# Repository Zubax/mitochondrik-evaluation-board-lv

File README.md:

# Mitochondrik Evaluation Board LV

Mitochondrik Evaluation Board LV is a basic reference design and an evaluation board for the
[Zubax Mitochnodrik LV](https://zubax.com/mitochondrik-lv) motor control module.
When combined with Mitochondrik LV, it makes a complete PMSM motor controller suitable for bench testing and evaluation of the
[Telega motor control technology](https://telega.zubax.com).
The device is also a specialized jig (fixture) that allows easy flashing and testing of all functions of Mitochondrik LV during manufacturing.

## Specifications

* Supply voltage range: 13--51 V.
* Max continuous current/peak phase current amplitude: 10/20 A.
* Designed strictly for indoor use.

### Telega configuration

In order to use the Mitochondrik Evaluation Board LV, the installed Mitochondrik LV has to be informed
of the parameters of the board.
To achieve this, upload the following configuration:

```yaml
# Mitochondrik Evaluation Board LV has transistors with R_DSon = 4 mohms, and 3 mohm shunts on phases A and B.
# Refer to the Mitochondrik-LV datasheet for the explanation of how the parameter values have been found.
vsi.bridge_resistance:    [0.004, 0.007, 0.004, 0.007, 0.004, 0.004]                            # [ohm]
vsi.phase_current_gain:   [33.333333333333, 33.333333333333, 8.333333333333, 8.333333333333]    # [ampere/volt]
vsi.phase_current_stderr: [0.2, 0.2, 0.1, 0.1]                                                  # [ampere]
vsi.thermistor_v2k:       [223.15, 100.0, 0.0]                                                  # for MCP9700

sys.debug: false            # Turn off the in-circuit debug interfaces to enhance EMI immunity.
sys.golden: sys. vsi.       # Retain these parameter groups across a factory reset.
```

Refer to the Telega Reference Manual for details.

## Features

All external signals of Mitochondrik LV are accessible via the pin headers.
Mitochondrik Evaluation Board LV also provides dedicated connectors for 2 Cyphal/CAN interfaces,
a Dronecode debug port, and one Aux connector for GPIO and RCPWM.
The motor phase wires and the DC link input are connected via M3 screw terminals.

A switch has been implemented which prevents powering the device if Mitochondrik LV is not installed or installed incorrectly.
Thanks to this feature, it is not required to remove the power supply every time before insertion of Mitochondrik LV.
The Mitochondrik presence pin is low when Mitochondrik is inserted.
Then, CAN_VDD should be set high, which turns on Q9, which then turns on Q11, allowing VDC to power the device.
The CAN_VDD is connected to the GPIO PA4 of Zubax Babel, which would turn on the power supply during testing.
The power supply switch is arranged in logic OR configuration, which means it's enable pin is attached to both of Babels
and either one of them can turn it on.
Check out the hardware schematic below:

A mechanical key is introduced to prevent incorrect insertion of Mitochondrik LV.

Headers are available to install the [Babel-Babel production tool](https://github.com/Zubax/Babel-Babel)
directly to the Mitochondrik Evaluation Board LV PCB without the need for an external adapter PCB.

| Stacked Babel-Babel | Babel-Babel headers |
| ------------------- | ------------------- |
|   |   |

## Manufacturing instructions

For details on the manufacturing process of the device, check the
instructions at [manufacturing document](/docs/manufacturing.md).

## Release notes

Newest entries at the top.

### Mitochondrik Evaluation Board LV v1.2 (2023)

* P-Channel mosfet for safety insertion changed from SQJ459EP-T1_GE3 to RQ3L070ATTB due to availability issue
* Alternative part added for FDMS86368-F085

### Mitochondrik Evaluation Board LV v1.1 (2023)

* Bug fix for CANVDD not connected to protection circuit
* Added CANVDD supply for consumer version
* Added connecto to adapter for ribbon to connect top part of adapter to the bottom part

### Mitochondrik Evaluation Board LV v1.0 (2021)

* The original version.

### License

This project is licensed under the terms of [CC-BY 4.0](https://creativecommons.org/licenses/by/4.0/).

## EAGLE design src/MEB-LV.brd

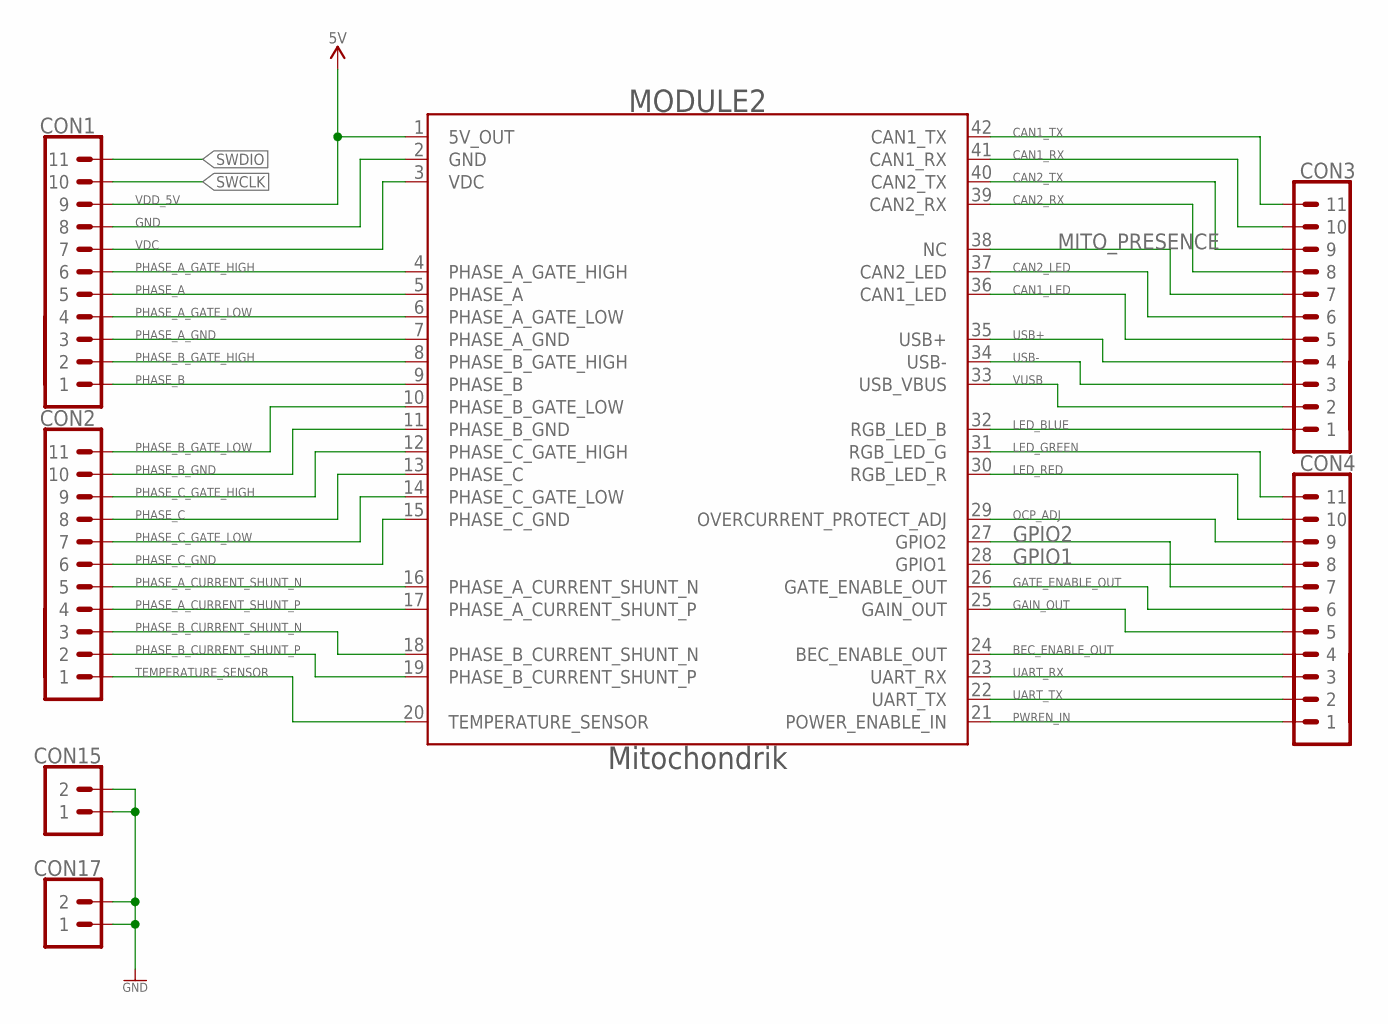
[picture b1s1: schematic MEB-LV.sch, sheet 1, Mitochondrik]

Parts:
CON1, CON2, CON3, CON4: PINHEAD_1X11-2.54_STRAIGHT_MALE; 1X11-PTH-2.54; DIGIKEY# S1022EC-11-ND
CON15, CON17: PINHEAD_1X02-2.54; 1X02-PTH-2.54; DIGIKEY# S1041E-02-ND
MODULE2: MITOCHONDRIK

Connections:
BEC_ENABLE_OUT: CON4.4, MODULE2.24 (BEC_ENABLE_OUT); also elsewhere on the board
CAN1_LED: CON3.5, MODULE2.36 (CAN1_LED); also elsewhere on the board
CAN1_RX: CON3.10, MODULE2.41 (CAN1_RX); also elsewhere on the board
CAN1_TX: CON3.11, MODULE2.42 (CAN1_TX); also elsewhere on the board
CAN2_LED: CON3.6, MODULE2.37 (CAN2_LED); also elsewhere on the board
CAN2_RX: CON3.8, MODULE2.39 (CAN2_RX); also elsewhere on the board
CAN2_TX: CON3.9, MODULE2.40 (CAN2_TX); also elsewhere on the board
GAIN_OUT: CON4.5, MODULE2.25 (GAIN_OUT); also elsewhere on the board
GATE_ENABLE_OUT: CON4.6, MODULE2.26 (GATE_ENABLE_OUT); also elsewhere on the board
GND: CON1.8, CON15.1, CON15.2, CON17.1, CON17.2, MODULE2.2 (GND); also elsewhere on the board
GPIO1: CON4.8, MODULE2.28 (GPIO1); also elsewhere on the board
GPIO2: CON4.7, MODULE2.27 (GPIO2); also elsewhere on the board
LED_BLUE: CON3.1, MODULE2.32 (RGB_LED_B); also elsewhere on the board
LED_GREEN: CON4.11, MODULE2.31 (RGB_LED_G); also elsewhere on the board
LED_RED: CON4.10, MODULE2.30 (RGB_LED_R); also elsewhere on the board
MITO_PRESENCE: CON3.7, MODULE2.38 (NC); also elsewhere on the board
OCP_ADJ: CON4.9, MODULE2.29 (OVERCURRENT_PROTECT_ADJ)
PHASE_A: CON1.5, MODULE2.5 (PHASE_A); also elsewhere on the board
PHASE_A_CURRENT_SHUNT_N: CON2.5, MODULE2.16 (PHASE_A_CURRENT_SHUNT_N); also elsewhere on the board
PHASE_A_CURRENT_SHUNT_P: CON2.4, MODULE2.17 (PHASE_A_CURRENT_SHUNT_P); also elsewhere on the board
PHASE_A_GATE_HIGH: CON1.6, MODULE2.4 (PHASE_A_GATE_HIGH); also elsewhere on the board
PHASE_A_GATE_LOW: CON1.4, MODULE2.6 (PHASE_A_GATE_LOW); also elsewhere on the board
PHASE_A_GND: CON1.3, MODULE2.7 (PHASE_A_GND); also elsewhere on the board
PHASE_B: CON1.1, MODULE2.9 (PHASE_B); also elsewhere on the board
PHASE_B_CURRENT_SHUNT_N: CON2.3, MODULE2.18 (PHASE_B_CURRENT_SHUNT_N); also elsewhere on the board
PHASE_B_CURRENT_SHUNT_P: CON2.2, MODULE2.19 (PHASE_B_CURRENT_SHUNT_P); also elsewhere on the board
PHASE_B_GATE_HIGH: CON1.2, MODULE2.8 (PHASE_B_GATE_HIGH); also elsewhere on the board
PHASE_B_GATE_LOW: CON2.11, MODULE2.10 (PHASE_B_GATE_LOW); also elsewhere on the board
PHASE_B_GND: CON2.10, MODULE2.11 (PHASE_B_GND); also elsewhere on the board
PHASE_C: CON2.8, MODULE2.13 (PHASE_C); also elsewhere on the board
PHASE_C_GATE_HIGH: CON2.9, MODULE2.12 (PHASE_C_GATE_HIGH); also elsewhere on the board
PHASE_C_GATE_LOW: CON2.7, MODULE2.14 (PHASE_C_GATE_LOW); also elsewhere on the board
PHASE_C_GND: CON2.6, MODULE2.15 (PHASE_C_GND); also elsewhere on the board
PWREN_IN: CON4.1, MODULE2.21 (POWER_ENABLE_IN)
SWCLK: CON1.10; also elsewhere on the board
SWDIO: CON1.11; also elsewhere on the board
TEMPERATURE_SENSOR: CON2.1, MODULE2.20 (TEMPERATURE_SENSOR); also elsewhere on the board
UART_RX: CON4.3, MODULE2.23 (UART_RX); also elsewhere on the board
UART_TX: CON4.2, MODULE2.22 (UART_TX); also elsewhere on the board
USB+: CON3.4, MODULE2.35 (USB+); also elsewhere on the board
USB-: CON3.3, MODULE2.34 (USB-); also elsewhere on the board
VDC: CON1.7, MODULE2.3 (VDC); also elsewhere on the board
VDD_5V: CON1.9, MODULE2.1 (5V_OUT); also elsewhere on the board
VUSB: CON3.2, MODULE2.33 (USB_VBUS); also elsewhere on the board

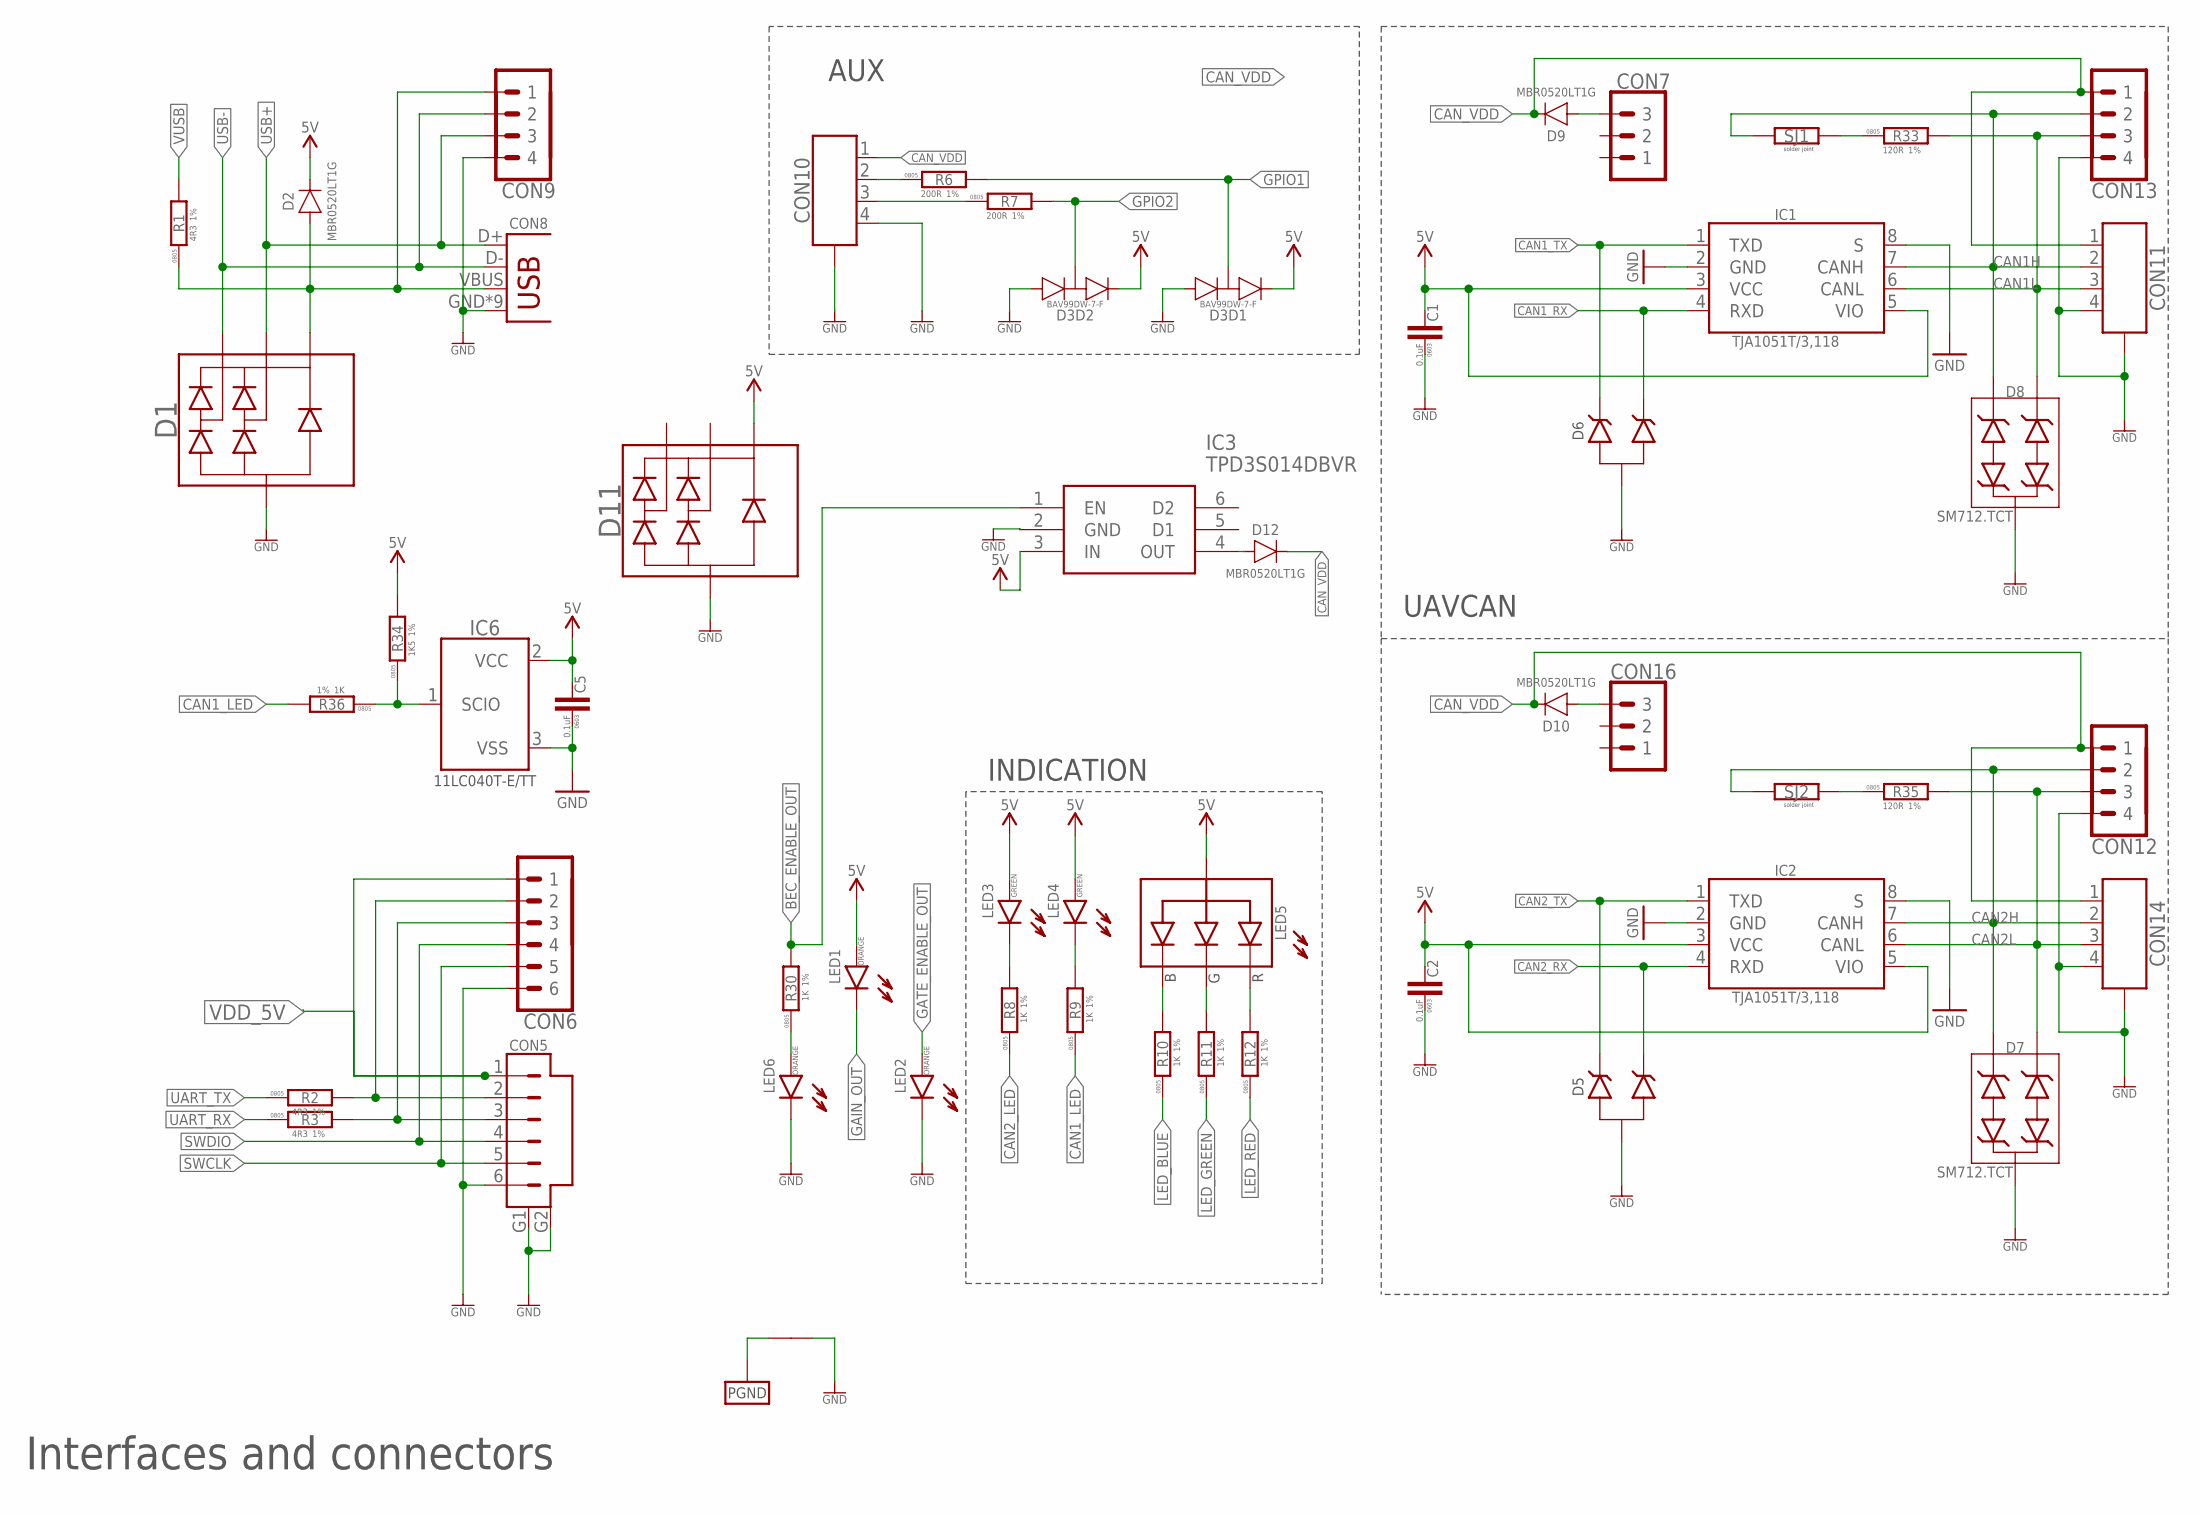
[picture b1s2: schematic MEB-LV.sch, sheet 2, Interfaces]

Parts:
C1, C2, C5: 0.1uF; C0603; DIGIKEY# 1276-1938-1-ND
CON5: CON-6P-SM06B; SM06B
CON6: PINHEAD_1X06-2.54-FEMALE; 1X06-PTH-2.54-FEMALE
CON7, CON16: PINHEAD_1X03-PBS3; PBS3
CON8: USB-1; -10118193-0001LF
CON9, CON12, CON13: PINHEAD_1X04-PBS4; PBS4
CON10, CON11, CON14: CON-4P-TABS-JST_GH-RA; JST_GH-4P-RA
D1, D11: PRTR5V0U2X; SOT143B
D2, D9, D10, D12: MBR0520L-SOD123; SOD123
D3: BAV99DW; SOT363
D5, D6: ESDA6V1L; SOT23B-3
D7, D8: SM712; SOT23B-3
IC1, IC2: TJA1051-SO8; SOIC8
IC3: TPD3S014DBVR; SOT95P280X145-6N
IC6: 11LC040T-E/TT; SOT23B-3
J1: CONNECTION-SMD; CONNECTION
LED1, LED2, LED6: ORANGE; LED0603; DIGIKEY# 754-1120-1-ND
LED3, LED4: GREEN; LED0603; DIGIKEY# 754-1116-1-ND
LED5: LTST-C19HE1WT; 0606
R1: 4R3; R0805
R2, R3: 4R3; R0805; DIGIKEY# 311-4.3ARTR-ND
R6, R7: 200R; R0805
R8, R9, R10, R11, R12, R30, R36: 1K; R0805; DIGIKEY# YAG1240CT-ND
R33, R35: 120R; R0805; DIGIKEY# 311-120CRCT-ND
R34: 1K5; R0805
SJ1, SJ2: SOLDER_JOINT; RES_0

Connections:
BEC_ENABLE_OUT: IC3.1 (EN), R30.2; also elsewhere on the board
CAN1H: CON11.2, CON13.2, D8.1 (C3), IC1.7 (CANH), SJ1.1
CAN1L: CON11.3, CON13.3, D8.2 (C2), IC1.6 (CANL), R33.2
CAN1_LED: R9.1, R36.2; also elsewhere on the board
CAN1_RX: D6.2 (C1), IC1.4 (RXD); also elsewhere on the board
CAN1_TX: D6.1 (C), IC1.1 (TXD); also elsewhere on the board
CAN2H: CON12.2, CON14.2, D7.1 (C3), IC2.7 (CANH), SJ2.1
CAN2L: CON12.3, CON14.3, D7.2 (C2), IC2.6 (CANL), R35.2
CAN2_LED: R8.1; also elsewhere on the board
CAN2_RX: D5.2 (C1), IC2.4 (RXD); also elsewhere on the board
CAN2_TX: D5.1 (C), IC2.1 (TXD); also elsewhere on the board
CAN_VDD: CON10.1, CON11.1, CON12.1, CON13.1, CON14.1, D9.C, D10.C, D12.C; also elsewhere on the board
GAIN_OUT: LED1.C; also elsewhere on the board
GATE_ENABLE_OUT: LED2.A; also elsewhere on the board
GND: C1.1, C2.1, C5.1, CON5.6, CON5.G1, CON5.G2, CON6.6, CON8.GND, CON8.GND1 (GND), CON8.GND2 (GND), CON8.GND3 (GND), CON8.GND4 (GND), CON8.P$1 (GND), CON8.P$2 (GND), CON8.P$3 (GND), CON8.P$4 (GND), CON9.4, CON10.4, CON10.M$0 (GND), CON10.M$1 (GND), CON11.4, CON11.M$0 (GND), CON11.M$1 (GND), CON12.4, CON13.4, CON14.4, CON14.M$0 (GND), CON14.M$1 (GND), D1.1 (C), D3.1 (A), D3.4 (A), D5.3 (A), D6.3 (A), D7.3, D8.3, D11.1 (C), IC1.2 (GND), IC1.8 (S), IC2.2 (GND), IC2.8 (S), IC3.2 (GND), IC6.3 (VSS), J1.P$2, LED2.C, LED6.C; also elsewhere on the board
GPIO1: D3.6 (COMMON), R6.2; also elsewhere on the board
GPIO2: D3.3 (COMMON), R7.2; also elsewhere on the board
LED_BLUE: R10.1; also elsewhere on the board
LED_GREEN: R11.1; also elsewhere on the board
LED_RED: R12.1; also elsewhere on the board
unnamed: LED6.A, R30.1
unnamed: CON7.3, D9.A
unnamed: CON16.3, D10.A
unnamed: CON5.2, CON6.2, R2.2
unnamed: D12.A, IC3.4 (OUT)
unnamed: LED4.C, R9.2
unnamed: LED3.C, R8.2
unnamed: R33.1, SJ1.2
unnamed: CON10.2, R6.1
unnamed: R35.1, SJ2.2
unnamed: CON10.3, R7.1
unnamed: LED5.R, R12.2
unnamed: LED5.G, R11.2
unnamed: LED5.B, R10.2
unnamed: CON5.3, CON6.3, R3.2
OIUOIUIOU: IC6.1 (SCIO), R34.1, R36.1
PGND: J1.P$1; also elsewhere on the board
SWCLK: CON5.5, CON6.5; also elsewhere on the board
SWDIO: CON5.4, CON6.4; also elsewhere on the board
UART_RX: R3.1; also elsewhere on the board
UART_TX: R2.1; also elsewhere on the board
USB+: CON8.D+, CON9.3, D1.3 (D2); also elsewhere on the board
USB-: CON8.D-, CON9.2, D1.2 (D1); also elsewhere on the board
USB_VBUS: CON8.VBUS, CON9.1, D1.4 (A), D2.A, R1.1
VDD_5V: C1.2, C2.2, C5.2, CON5.1, CON6.1, D2.C, D3.2 (C), D3.5 (C), D11.4 (A), IC1.3 (VCC), IC1.5 (VIO), IC2.3 (VCC), IC2.5 (VIO), IC3.3 (IN), IC6.2 (VCC), LED1.A, LED3.A, LED4.A, LED5.+ (A), R34.2; also elsewhere on the board
VUSB: R1.2; also elsewhere on the board

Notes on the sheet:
Interfaces and connectors
UAVCAN
AUX
INDICATION

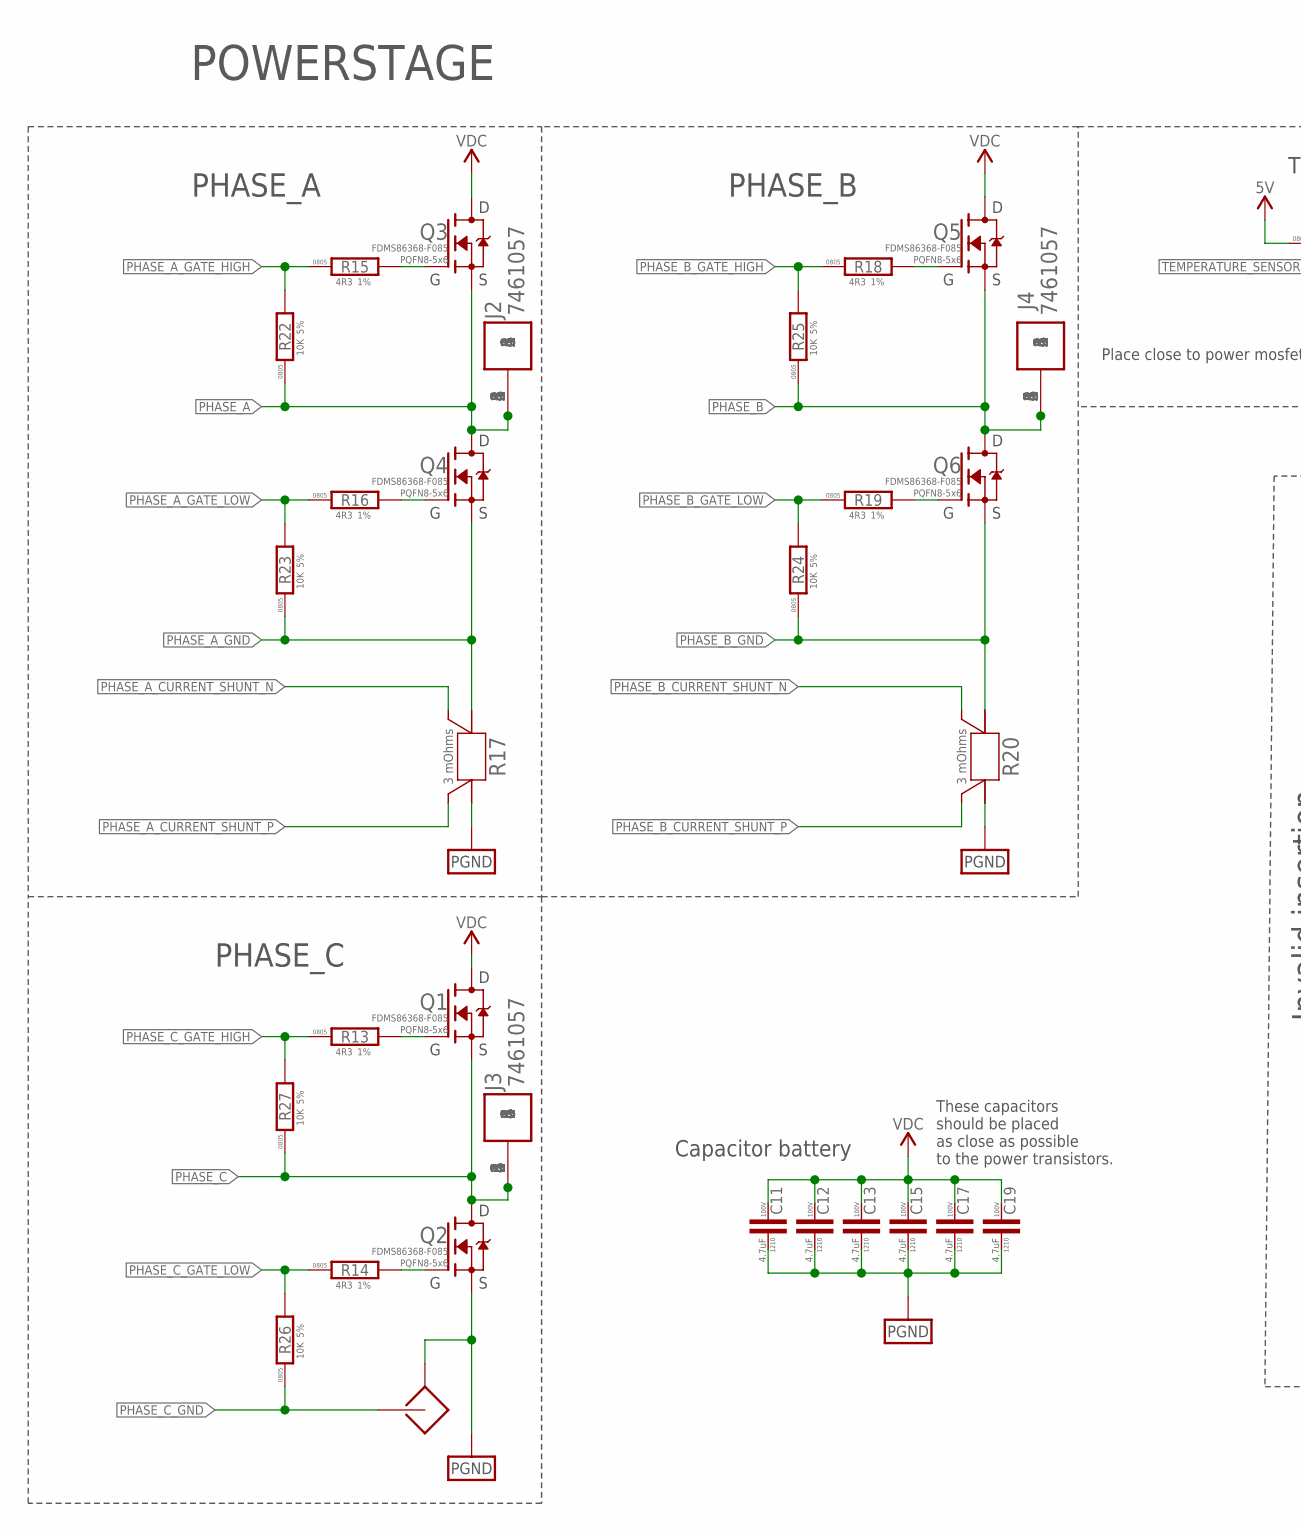
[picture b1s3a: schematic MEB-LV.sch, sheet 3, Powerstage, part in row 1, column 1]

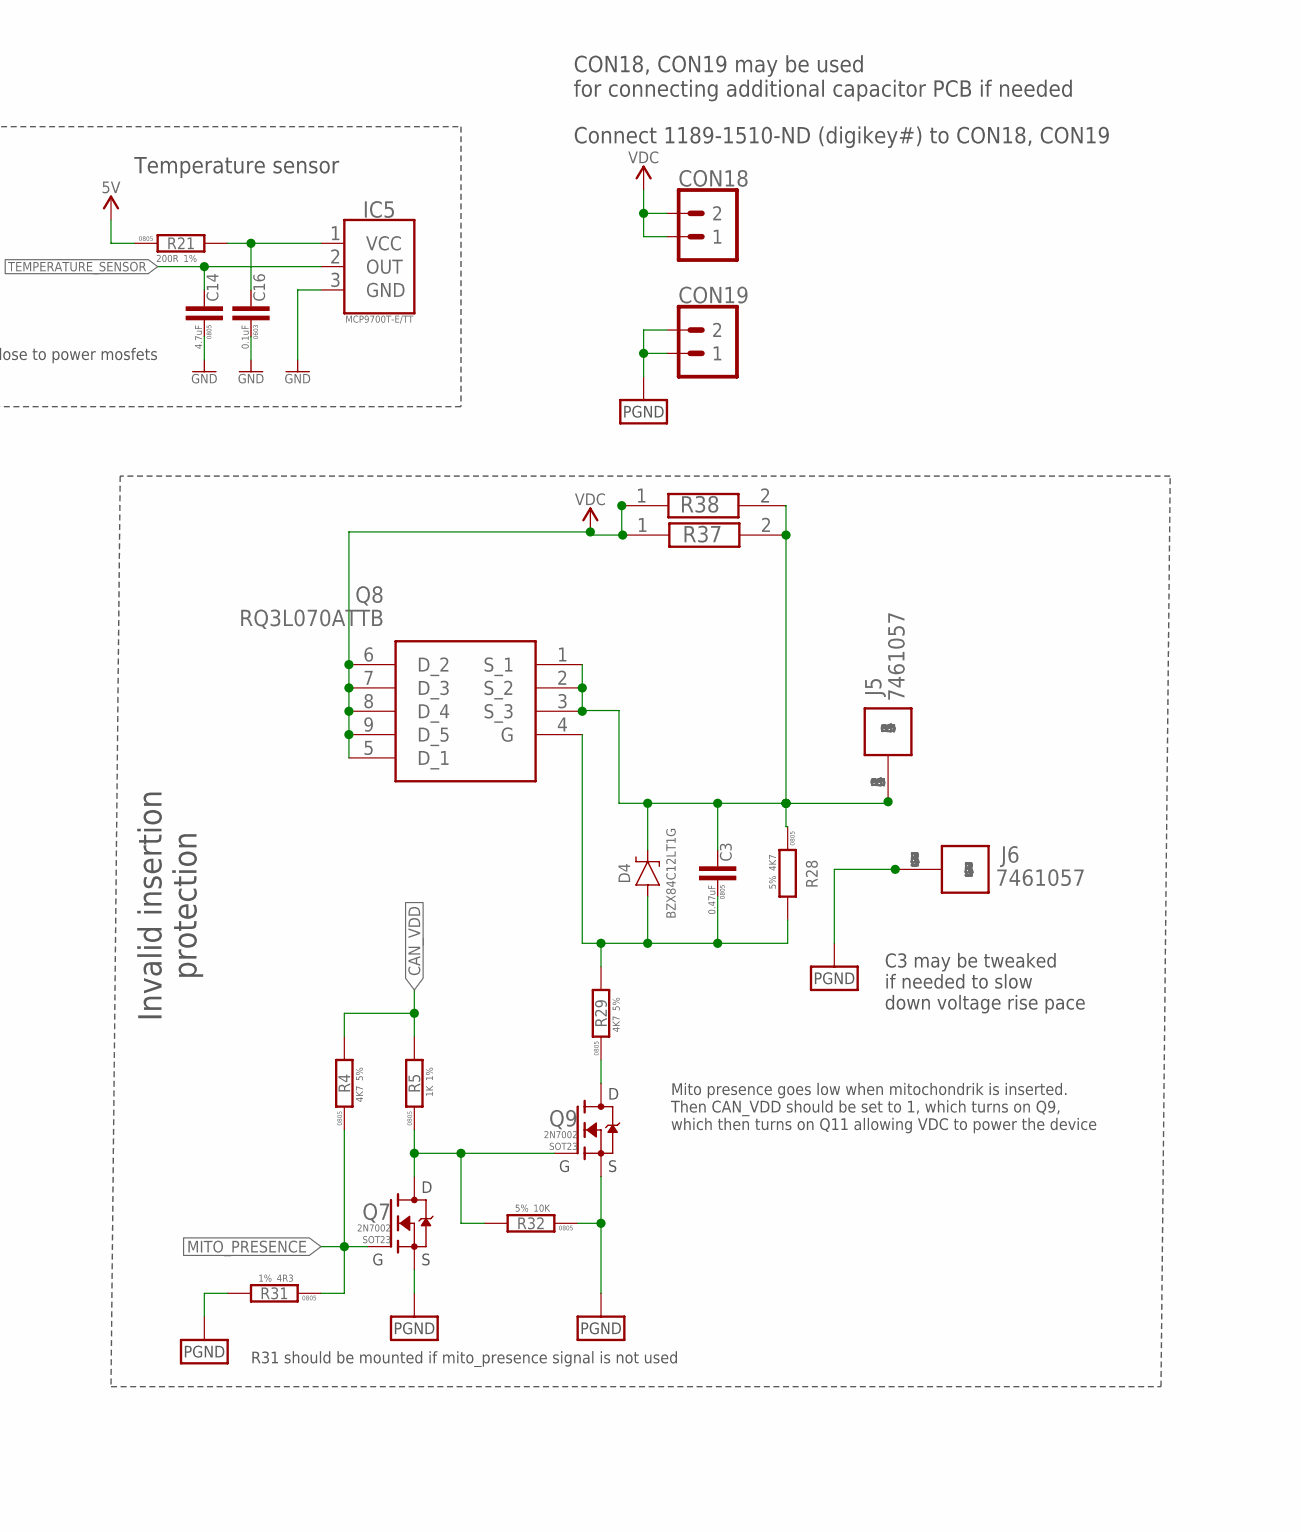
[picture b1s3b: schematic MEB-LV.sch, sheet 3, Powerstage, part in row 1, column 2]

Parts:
C3: 0.47uF; C0805
C11, C12, C13, C15, C17, C19: 4.7uF; C1210; VOLTAGE 100V; DIGIKEY# 490-14484-1-ND
C14: 4.7uF; C0805; DIGIKEY# 1276-2415-1-ND
C16: 0.1uF; C0603; DIGIKEY# 1276-1938-1-ND
CON18, CON19: PINHEAD_1X02-2.54; 1X02-PTH-2.54
D4: BZX84C12; SOT23
IC5: MCP9700T-E/TT-SOT23; SOT23B-3
J2, J3, J4, J5, J6: 7461057
Q1, Q2, Q3, Q4, Q5, Q6: FDMS86368-F085; PQFN8_5X6
Q7, Q9: 2N7002; SOT23; DIGIKEY# 2N7002NCT-ND
Q8: RQ3L070ATTB
R4, R28, R29: 4K7; R0805; DIGIKEY# YAG3364CT-ND
R5: 1K; R0805; DIGIKEY# YAG1240CT-ND
R13, R14, R15, R16, R18, R19, R31: 4R3; R0805; DIGIKEY# 311-4.3ARTR-ND
R17, R20: 3 mOhms; R2512-KELVIN; LCSC# C76247
R21: 200R; R0805; DIGIKEY# 13-RT0805FRE07200RLCT-ND
R22, R23, R24, R25, R26, R27, R32: 10K; R0805; DIGIKEY# YAG1239CT-ND
R37, R38: PMR18EZPJ000; RESC3216X42N
S1: SENSE; SENSE-0.6

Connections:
CAN_VDD: R4.2, R5.2; also elsewhere on the board
GND: C14.1, C16.1, IC5.3 (GND); also elsewhere on the board
MITO_PRESENCE: Q7.1 (G), R4.1, R31.1; also elsewhere on the board
unnamed: C16.2, IC5.1 (VCC), R21.2
unnamed: Q5.4 (G), R18.2
unnamed: Q6.4 (G), R19.2
unnamed: Q7.3 (D), Q9.1 (G), R5.1, R32.2
unnamed: Q3.4 (G), R15.2
unnamed: Q4.4 (G), R16.2
unnamed: Q9.3 (D), R29.1
unnamed: Q1.4 (G), R13.2
unnamed: Q2.4 (G), R14.2
unnamed: C3.2, D4.3 (C), J5.1, J5.2, J5.3, J5.4, J5.5, J5.6, Q8.1 (S_1), Q8.2 (S_2), Q8.3 (S_3), R28.1, R37.2, R38.2
PGND: C11.1, C12.1, C13.1, C15.1, C17.1, C19.1, CON19.1, CON19.2, J6.1, J6.2, J6.3, J6.4, J6.5, J6.6, Q2.1 (S), Q2.2 (S), Q2.3 (S), Q7.2 (S), Q9.2 (S), R17.2, R17.22 (2), R20.2, R20.22 (2), R31.2, R32.1, S1.SHELL (SHELLL); also elsewhere on the board
PHASE_A: J2.1, J2.2, J2.3, J2.4, J2.5, J2.6, Q3.1 (S), Q3.2 (S), Q3.3 (S), Q4.5 (D), Q4.6 (D), Q4.7 (D), Q4.8 (D), Q4.P$1 (D), R22.1; also elsewhere on the board
PHASE_A_CURRENT_SHUNT_N: R17.S1; also elsewhere on the board
PHASE_A_CURRENT_SHUNT_P: R17.S2; also elsewhere on the board
PHASE_A_GATE_HIGH: R15.1, R22.2; also elsewhere on the board
PHASE_A_GATE_LOW: R16.1, R23.2; also elsewhere on the board
PHASE_A_GND: Q4.1 (S), Q4.2 (S), Q4.3 (S), R17.1, R17.11 (1), R23.1; also elsewhere on the board
PHASE_B: J4.1, J4.2, J4.3, J4.4, J4.5, J4.6, Q5.1 (S), Q5.2 (S), Q5.3 (S), Q6.5 (D), Q6.6 (D), Q6.7 (D), Q6.8 (D), Q6.P$1 (D), R25.1; also elsewhere on the board
PHASE_B_CURRENT_SHUNT_N: R20.S1; also elsewhere on the board
PHASE_B_CURRENT_SHUNT_P: R20.S2; also elsewhere on the board
PHASE_B_GATE_HIGH: R18.1, R25.2; also elsewhere on the board
PHASE_B_GATE_LOW: R19.1, R24.2; also elsewhere on the board
PHASE_B_GND: Q6.1 (S), Q6.2 (S), Q6.3 (S), R20.1, R20.11 (1), R24.1; also elsewhere on the board
PHASE_C: J3.1, J3.2, J3.3, J3.4, J3.5, J3.6, Q1.1 (S), Q1.2 (S), Q1.3 (S), Q2.5 (D), Q2.6 (D), Q2.7 (D), Q2.8 (D), Q2.P$1 (D), R27.1; also elsewhere on the board
PHASE_C_GATE_HIGH: R13.1, R27.2; also elsewhere on the board
PHASE_C_GATE_LOW: R14.1, R26.2; also elsewhere on the board
PHASE_C_GND: R26.1, S1.IN; also elsewhere on the board
SFGKDLS: C3.1, D4.1 (A), Q8.4 (G), R28.2, R29.2
TEMPERATURE_SENSOR: C14.2, IC5.2 (OUT); also elsewhere on the board
VDC: C11.2, C12.2, C13.2, C15.2, C17.2, C19.2, CON18.1, CON18.2, Q1.5 (D), Q1.6 (D), Q1.7 (D), Q1.8 (D), Q1.P$1 (D), Q3.5 (D), Q3.6 (D), Q3.7 (D), Q3.8 (D), Q3.P$1 (D), Q5.5 (D), Q5.6 (D), Q5.7 (D), Q5.8 (D), Q5.P$1 (D), Q8.5 (D_1), Q8.6 (D_2), Q8.7 (D_3), Q8.8 (D_4), Q8.9 (D_5), R37.1, R38.1; also elsewhere on the board
VDD_5V: R21.1; also elsewhere on the board

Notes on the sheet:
PHASE_B
PHASE_A
PHASE_C
Capacitor battery
These capacitors should be placed as close as possible to the power transistors.
Temperature sensor
Place close to power mosfets
POWERSTAGE
Invalid insertion protection
R31 should be mounted if mito_presence signal is not used
Mito presence goes low when mitochondrik is inserted. Then CAN_VDD should be set to 1, which turns on Q9, which then turns on Q11 allowing VDC to power the device
CON18, CON19 may be used for connecting additional capacitor PCB if needed
Connect 1189-1510-ND (digikey#) to CON18, CON19
C3 may be tweaked if needed to slow down voltage rise pace

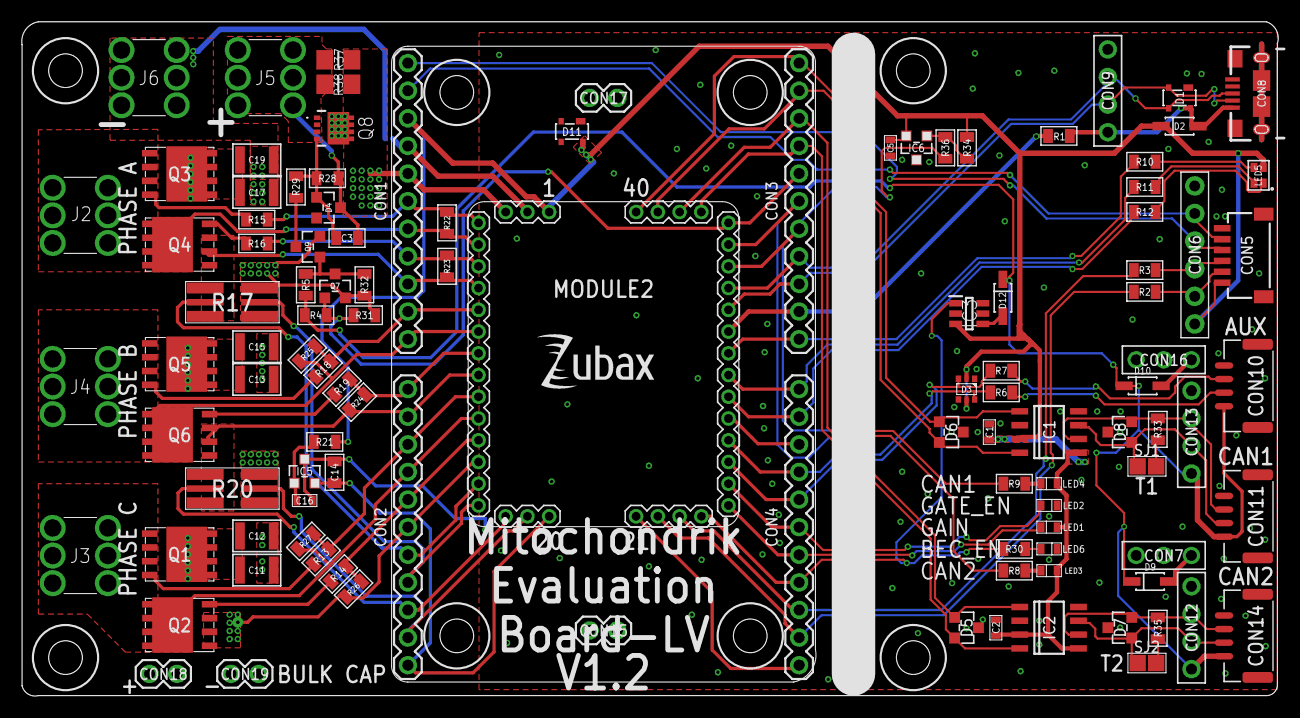
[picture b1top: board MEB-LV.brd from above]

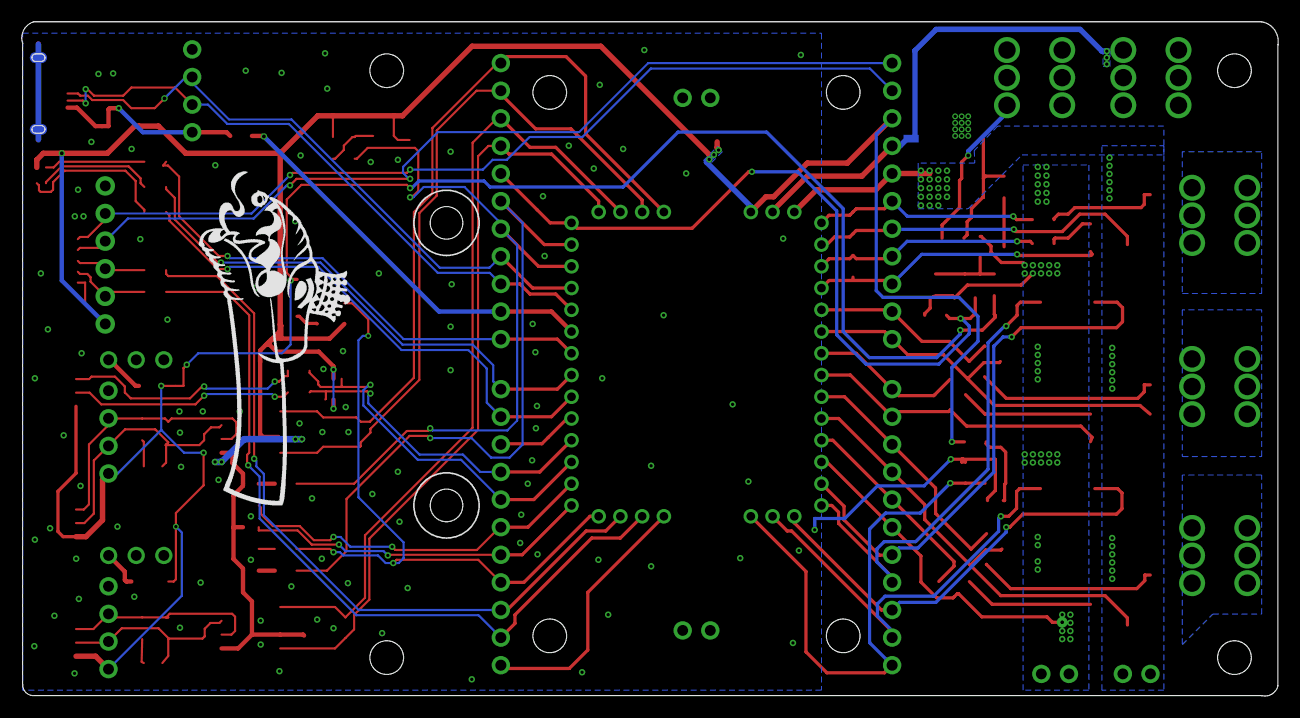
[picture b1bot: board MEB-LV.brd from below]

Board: 2 copper layers, 115.6 x 62.0 mm, 114 parts (2 on the bottom side), 78 nets.

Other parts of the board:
U$1: DRAGON-30X13
U$2: ZUBAX_LOGO_5X10
U$3: BABEL-BABEL

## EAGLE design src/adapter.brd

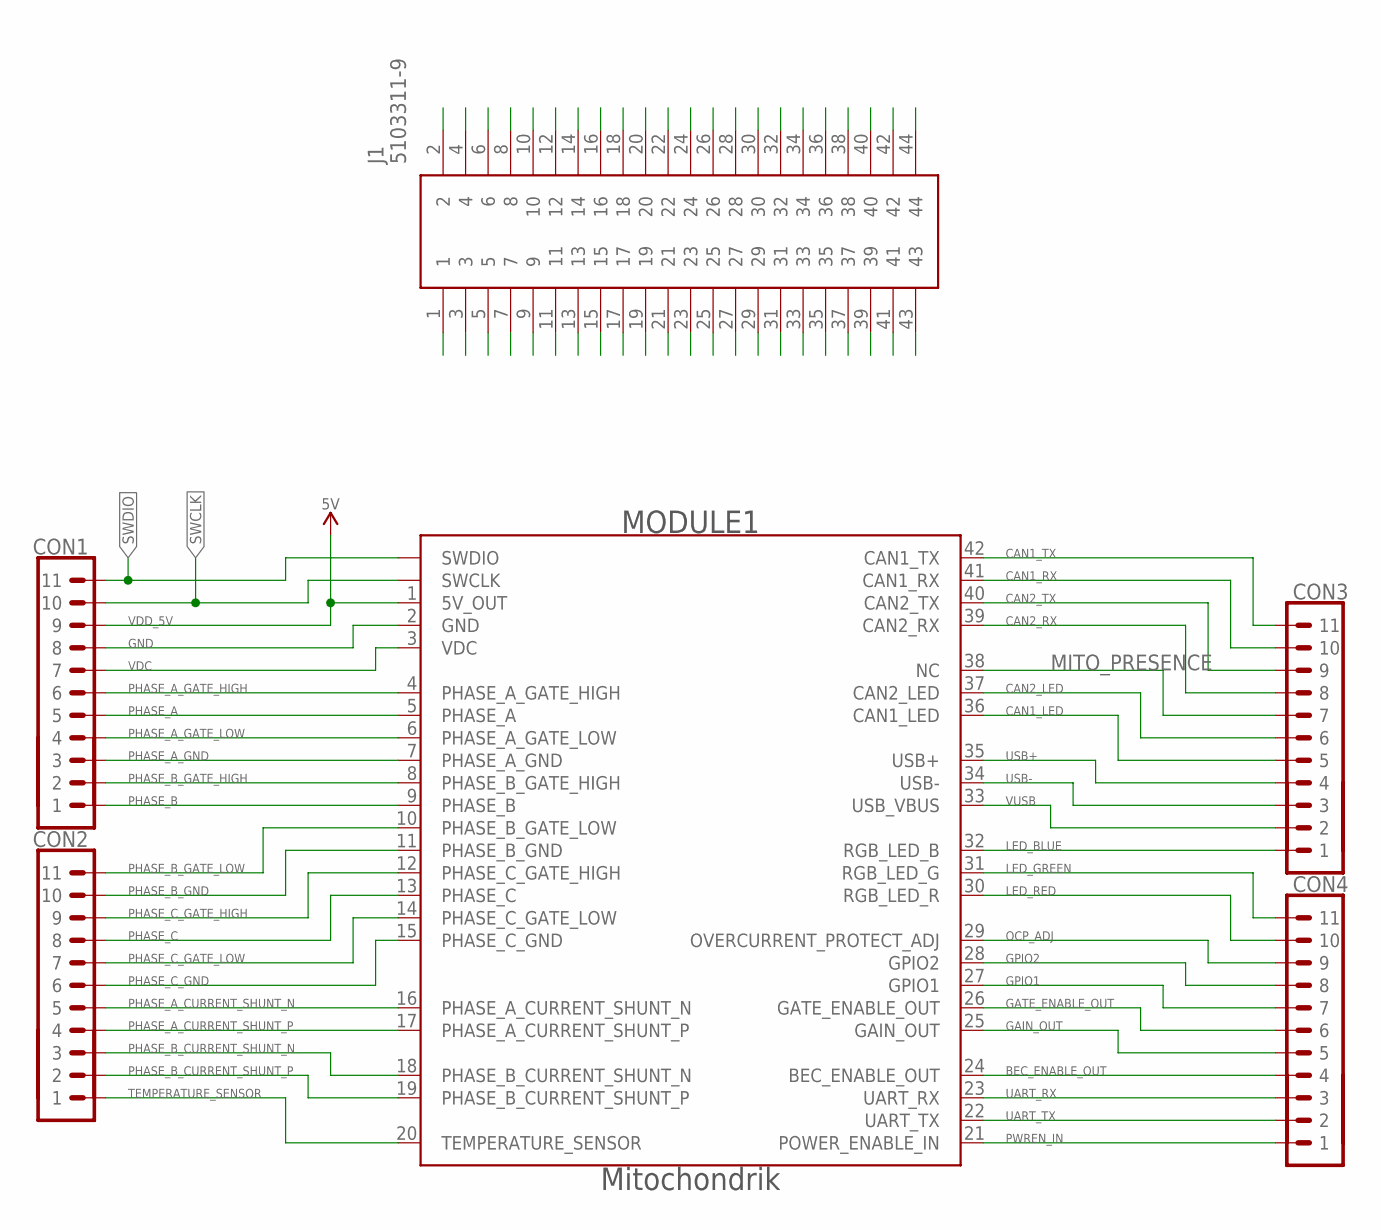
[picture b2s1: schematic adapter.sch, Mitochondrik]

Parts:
CON1, CON2, CON3, CON4: PINHEAD_1X11-2.54_STRAIGHT_FEMALE; 1X11-PTH-2.54-FEMALE; DIGIKEY# S7009-ND
J1: 5103311-9; SHDRRA44W66P254_2X22_6337X986X
MODULE1: MITOHONDRIQUE_POGO-POGO; MITOHONDRIQUE-POGO

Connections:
BEC_ENABLE_OUT: CON4.4, J1.37, MODULE1.24 (BEC_ENABLE_OUT)
CAN1_LED: CON3.5, J1.13, MODULE1.36 (CAN1_LED)
CAN1_RX: CON3.10, J1.3, MODULE1.41 (CAN1_RX)
CAN1_TX: CON3.11, J1.1, MODULE1.42 (CAN1_TX)
CAN2_LED: CON3.6, J1.11, MODULE1.37 (CAN2_LED)
CAN2_RX: CON3.8, J1.7, MODULE1.39 (CAN2_RX)
CAN2_TX: CON3.9, J1.5, MODULE1.40 (CAN2_TX)
GAIN_OUT: CON4.5, J1.35, MODULE1.25 (GAIN_OUT)
GATE_ENABLE_OUT: CON4.6, J1.33, MODULE1.26 (GATE_ENABLE_OUT)
GND: CON1.8, J1.8, MODULE1.2 (GND)
GPIO1: CON4.7, J1.31, MODULE1.27 (GPIO1)
GPIO2: CON4.8, J1.29, MODULE1.28 (GPIO2)
LED_BLUE: CON3.1, J1.21, MODULE1.32 (RGB_LED_B)
LED_GREEN: CON4.11, J1.23, MODULE1.31 (RGB_LED_G)
LED_RED: CON4.10, J1.25, MODULE1.30 (RGB_LED_R)
MITO_PRESENCE: CON3.7, J1.9, MODULE1.38 (NC)
OCP_ADJ: CON4.9, J1.27, MODULE1.29 (OVERCURRENT_PROTECT_ADJ)
PHASE_A: CON1.5, J1.14, MODULE1.5 (PHASE_A)
PHASE_A_CURRENT_SHUNT_N: CON2.5, J1.36, MODULE1.16 (PHASE_A_CURRENT_SHUNT_N)
PHASE_A_CURRENT_SHUNT_P: CON2.4, J1.38, MODULE1.17 (PHASE_A_CURRENT_SHUNT_P)
PHASE_A_GATE_HIGH: CON1.6, J1.12, MODULE1.4 (PHASE_A_GATE_HIGH)
PHASE_A_GATE_LOW: CON1.4, J1.16, MODULE1.6 (PHASE_A_GATE_LOW)
PHASE_A_GND: CON1.3, J1.18, MODULE1.7 (PHASE_A_GND)
PHASE_B: CON1.1, J1.22, MODULE1.9 (PHASE_B)
PHASE_B_CURRENT_SHUNT_N: CON2.3, J1.40, MODULE1.18 (PHASE_B_CURRENT_SHUNT_N)
PHASE_B_CURRENT_SHUNT_P: CON2.2, J1.42, MODULE1.19 (PHASE_B_CURRENT_SHUNT_P)
PHASE_B_GATE_HIGH: CON1.2, J1.20, MODULE1.8 (PHASE_B_GATE_HIGH)
PHASE_B_GATE_LOW: CON2.11, J1.24, MODULE1.10 (PHASE_B_GATE_LOW)
PHASE_B_GND: CON2.10, J1.26, MODULE1.11 (PHASE_B_GND)
PHASE_C: CON2.8, J1.30, MODULE1.13 (PHASE_C)
PHASE_C_GATE_HIGH: CON2.9, J1.28, MODULE1.12 (PHASE_C_GATE_HIGH)
PHASE_C_GATE_LOW: CON2.7, J1.32, MODULE1.14 (PHASE_C_GATE_LOW)
PHASE_C_GND: CON2.6, J1.34, MODULE1.15 (PHASE_C_GND)
PWREN_IN: CON4.1, J1.43, MODULE1.21 (POWER_ENABLE_IN)
SWCLK: CON1.10, J1.4, MODULE1.SWCLK
SWDIO: CON1.11, J1.2, MODULE1.SWDIO
TEMPERATURE_SENSOR: CON2.1, J1.44, MODULE1.20 (TEMPERATURE_SENSOR)
UART_RX: CON4.3, J1.39, MODULE1.23 (UART_RX)
UART_TX: CON4.2, J1.41, MODULE1.22 (UART_TX)
USB+: CON3.4, J1.15, MODULE1.35 (USB+)
USB-: CON3.3, J1.17, MODULE1.34 (USB-)
VDC: CON1.7, J1.10, MODULE1.3 (VDC)
VDD_5V: CON1.9, J1.6, MODULE1.1 (5V_OUT)
VUSB: CON3.2, J1.19, MODULE1.33 (USB_VBUS)
